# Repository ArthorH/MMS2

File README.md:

# modular_system_mini
mini verison of modular system connectable as bus 

# if you want to add new board
1. create new folder with name of the board
2. create new project in kicad in this folder

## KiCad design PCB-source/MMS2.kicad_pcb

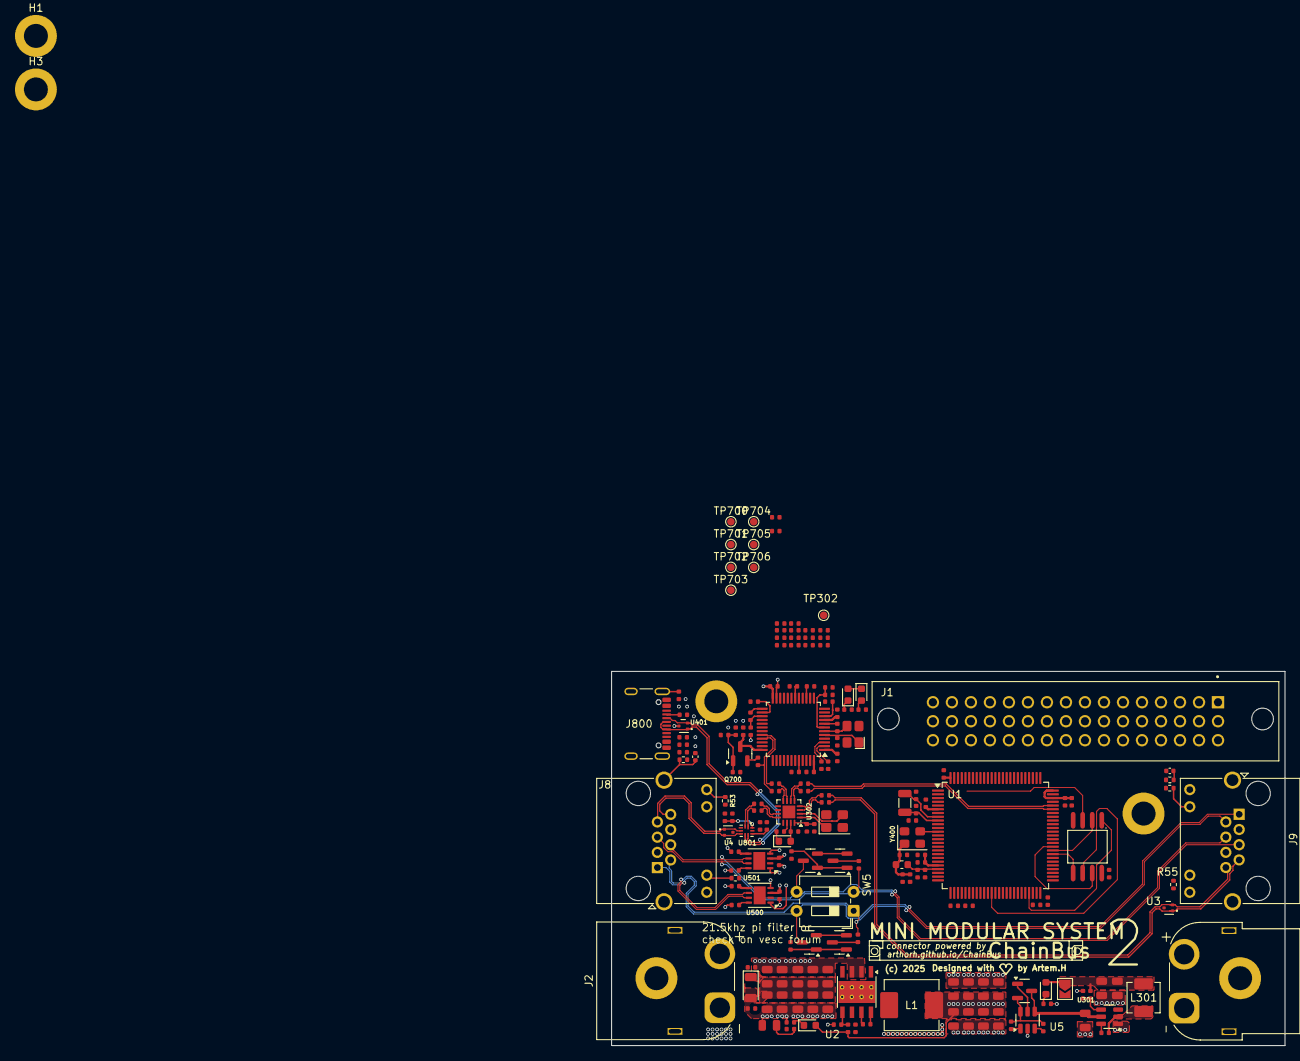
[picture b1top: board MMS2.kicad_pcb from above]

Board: 2 copper layers, 90.0 x 50.0 mm, 188 parts (0 on the bottom side), 120 nets.

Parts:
C1, C2, C4, C5, C6, C7, C14, C15, C16: 10uF; C_0805
C3, C10, C17, C100, C312, C401, C402, C404, C405, C406, C415, C416, C420, C421, C422, C424, C426, C432, C500, C501, C502, C503, C701, C702, C703, C704, C705, C706, C800, C801, C900: 100nF; C_0402
C8, C9: 220nF; C_0805
C11, C12, C13, C18, C19, C20, C22, C23, C24, C25, C28: 22uF; C_0805
C27, C700, C904: 1uF; C_0402
C45, C46: 10n; C_0402_1005Metric
C313, C314: 18pF; C_0402
C400, C403, C423, C425, C902: 10uF; C_0402
C410: 4.7uF; C_0402
C427, C434: 2.2uF; C_0402
C707, C708: 33pF; C_0402
D1: SMF58CA; D_SOD-123FL
D2, D301, D402, D700, D701: Red; D_0603
FB401: FB_0603
H1, H2, H3, H4, H4#2, H4#3: M3 mount; MountingHole_3.2mm_M3_DIN965_Pad
J1: 86093488324755V1LF; AMPHENOL_86093488324755V1LF
J2: AMASS XT60; AMASS_XT60PW-M_1x02_P7.20mm_Horizontal
J7: AMASS XT60; AMASS_XT60PW-F_1x02_P7.20mm_Horizontal
J8, J9: RJ45_LED_Shielded; RJ45_Amphenol_RJHSE538X
J800: USB_C_Receptacle_USB2.0_16P; USB_C_Receptacle_GCT_USB4105-xx-A_16P_TopMnt_Horizontal
JP301: SolderJumper_2_Bridged; SolderJumper-2_P1.3mm_Open_TrianglePad1.0x1.5mm
L1: CMPI0630-100M 10uH 4A; L_TechFuse_SL0620
L301: 3.3uH; L_Changjiang_FXL0420
Q2, Q3, Q5, Q6, Q7: AO3400A; Q_SOT-23
Q700: MMST3904; SOT-23
R1, R2: 120Ω; R_0402
R3, R5, R7, R10, R307, R402, R403, R405, R500, R501, R701, R703, R705, R706, R707, R709, R713, R802, R804: 10kΩ; R_0402
R4, R8, R9: 24.9kΩ; R_0402
R6, R700, R702: 100kΩ; R_0402
R11: 33.2kΩ; R_0402
R12, R400, R712: 1.2kΩ; R_0402
R13: 680Ω; R_0402
R14, R15, R704, R708, R715, R716, R900, R901, R902, R903, R906, R907: 22Ω; R_0402
R51, R56: 33k; R_0402_1005Metric
R52, R53, R54, R55: 1k; R_0402_1005Metric
R308, R401: 1kΩ; R_0402
R404, R406, R409, R710, R714: 100Ω; R_0402
R407, R408: 220Ω; R_0402
R711: 39kΩ; R_0402
R800, R801: 5.1kΩ; R_0402
R803: 22kΩ; R_0402
R805: 330Ω; R_0402
SW5: SW_DIP_x02; SW_DIP_SPSTx02_Slide_6.7x6.64mm_W7.62mm_P2.54mm_LowProfile
TP302, TP700, TP701, TP702, TP703, TP704, TP705, TP706: TestPoint; TestPoint_Pad_D1.0mm
U1: STM32H563VGTx; LQFP-100_14x14mm_P0.5mm
U2: LMR36520ADDAR; Texas_HSOP-8-1EP_3.9x4.9mm_P1.27mm_ThermalVias
U3, U4, U401: TPD2EUSB30DRTR-TP; SOT-723
U5: LM74700; SOT-23-6
U100: W25Q128; SOIC-8_L5.3-W5.3-P1.27-LS8.0-BL
U301: TPS563200; SOT-23-6
U302: CH334P; QFN-16-1EP_3x3mm_P0.5mm_EP1.7x1.7mm
U500, U501: TJA1044GTK_3Z; HVSON-8-1EP_3x3mm_P0.65mm_EP1.6x2.4mm
U700: STM32F103CBTx; LQFP-48_7x7mm_P0.5mm
U801: FSUSB42UMX; UFQFN-10_1.4x1.8
X300: Q13FC1350000400; FC-135R_L3.2-W1.5
Y400: ASE-xxxMHz; Oscillator_SMD_Abracon_ASE-4Pin_3.2x2.5mm
Y700: Crystal_GND24; CRYSTAL-SMD_4P-L3.2-W2.5-BL
Y900: Crystal_GND24; Crystal_SMD_3225-4Pin_3.2x2.5mm

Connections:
+3V3: C100.1, C312.1, C400.1, C401.1, C402.1, C403.1, C404.1, C405.1, C406.1, C420.1, C421.1, C422.1, C425.1, C426.1, C432.1, C501.1, C503.1, C700.1, C701.1, C702.1, C703.1, C704.1, C705.1, FB401.2, Q700.3 (C), R403.1, R405.1, R409.1, R700.1, R701.1, R707.1, TP702.1, U1.6 (VBAT), U1.11 (VDD), U1.21 (VREF+), U1.28 (VDD), U1.50 (VDD), U1.73 (VDDUSB), U1.75 (VDD), U1.100 (VDD), U100.8 (VCC), U500.5 (VIO), U501.5 (VIO), U700.1 (VBAT), U700.9 (VDDA), U700.24 (VDD), U700.36 (VDD), U700.48 (VDD), U801.9 (VCC), Y400.1 (EN), Y400.4 (Vdd)
+5V: C500.2, C502.2, C904.1, D301.2, R709.1, U302.15 (5V), U500.3 (VCC), U501.3 (VCC)
+12V: J8.6, J9.6
/CAN auto terminator/CAN1.+: J8.5, J9.5, R2.1, SW5.2, U501.7 (CANH)
/CAN auto terminator/CAN1.-: J8.4, J9.4, Q6.3 (D), SW5.3, U501.6 (CANL)
/CAN auto terminator/CAN2.+: J8.2, J9.2, R1.1, SW5.1, U500.7 (CANH)
/CAN auto terminator/CAN2.-: J8.1, J9.1, Q3.3 (D), SW5.4, U500.6 (CANL)
/CAN auto terminator/CAN_AUTOTERM.1: Q5.1 (G), Q6.1 (G), R3.1
/CAN auto terminator/CAN_AUTOTERM.2: Q2.1 (G), Q3.1 (G), R5.1
/CAN_TR1/CAN.RX: U1.81 (PD0), U500.4 (RXD)
/CAN_TR1/CAN.TX: U1.82 (PD1), U500.1 (TXD)
/CAN_TR2/CAN.RX: U1.51 (PB12), U501.4 (RXD)
/CAN_TR2/CAN.TX: U1.52 (PB13), U501.1 (TXD)
/MCU/BOOT0: C410.1, R401.2, R402.1, U1.94 (BOOT0)
/MCU/BOOT_EN: R401.1, U1.93 (PB7)
/MCU/NRST: C415.1, R403.2, R404.1
/MCU/OSC32_IN: C314.1, U1.8 (PC14), X300.2
/MCU/OSC32_OUT: C313.1, U1.9 (PC15), X300.1
/MCU/OSC_IN: U1.12 (PH0), Y400.3 (OUT)
/MCU/QSPI1.CS: U1.47 (PB10), U100.1 (CS#)
/MCU/QSPI1.IO0: U1.58 (PD11), U100.5 (DI)
/MCU/QSPI1.IO1: U1.59 (PD12), U100.2 (DO)
/MCU/QSPI1.IO2: U1.1 (PE2), U100.3 (IO2)
/MCU/QSPI1.IO3: U1.60 (PD13), U100.7 (IO3)
/MCU/QSPI1.SCLK: U1.37 (PB2), U100.6 (CLK)
/MCU/STATUS_LED: R408.1, U1.4 (PE5)
/MCU/SWD.SWCLK: R704.2, R715.1, U1.76 (PA14(JTCK)
/MCU/SWD.SWDIO: R716.1, U1.72 (PA13(JTMS)
/MCU/SWD.~RST: R404.2, R708.1, U1.14 (NRST)
/MCU/USB_MCU.D+: R901.1, U1.71 (PA12)
/MCU/USB_MCU.D-: R900.1, U1.70 (PA11)
/MCU/USER_LED_1: R400.1, U1.2 (PE3)
/MCU/USER_LED_2: R407.1, U1.3 (PE4)
/MCU/USR_BTN: C416.1, R405.2, R406.1
/MCU/USR_BUTTON: R406.2, U1.5 (PE6)
/MCU/VCAP_1: C427.1, U1.48 (VCAP)
/MCU/VCAP_2: C434.1, U1.98 (VCAP)
/MCU/VDDA: C423.1, C424.1, FB401.1, U1.22 (VDDA)
/MMS_CONNECTOR_DOWNSTREAM/USB_MMS_CONN.D+: J9.8, R903.1, U3.2
/MMS_CONNECTOR_DOWNSTREAM/USB_MMS_CONN.D-: J9.7, R902.1, U3.1
/MMS_CONNECTOR_UPSTREAM/USB_MMS_CONN.D+: J8.8, U4.2, U801.5 (HSD1+)
/MMS_CONNECTOR_UPSTREAM/USB_MMS_CONN.D-: J8.7, U4.1, U801.4 (HSD1-)
/STlink-BMprobe/CLK: TP705.1, U700.37 (PA14)
/STlink-BMprobe/DIO: TP704.1, U700.34 (PA13)
/STlink-BMprobe/LED: D700.1, D701.2, U700.30 (PA9)
/STlink-BMprobe/ST-LINK.D+: R712.2, R907.1, U700.33 (PA12)
/STlink-BMprobe/ST-LINK.D-: R906.1, U700.32 (PA11)
/STlink-BMprobe/STLINK-BOOT0: R702.2, TP703.1, U700.44 (BOOT0)
/STlink-BMprobe/STLINK-OSC_IN: C707.1, U700.5 (PD0), Y700.1
/STlink-BMprobe/STLINK-OSC_OUT: C708.1, U700.6 (PD1), Y700.3
/STlink-BMprobe/STLINK-RST: C706.1, R700.2, U700.7 (NRST)
/STlink-BMprobe/STLINK_RX: TP701.1, U700.13 (PA3)
/STlink-BMprobe/STLINK_TX: TP700.1, U700.12 (PA2)
/STlink-BMprobe/USB_RENUM: R710.2, U700.38 (PA15)
/USB HUB/USBIN1.D+: R14.2, U801.1 (D+)
/USB HUB/USBIN1.D-: R15.2, U801.2 (D-)
/USB HUB/USBIN1_R.D+: R14.1, U302.12 (DPU)
/USB HUB/USBIN1_R.D-: R15.1, U302.11 (DMU)
/USB HUB/USBOUT1_R.D+: R903.2, U302.4 (DP4)
/USB HUB/USBOUT1_R.D-: R902.2, U302.3 (DM4)
/USB HUB/USBOUT2_R.D+: R907.2, U302.8 (DP2)
/USB HUB/USBOUT2_R.D-: R906.2, U302.7 (DM2)
/USB HUB/USB_MCU_R.D+: R901.2, U302.6 (DP3)
/USB HUB/USB_MCU_R.D-: R900.2, U302.5 (DM3)
/USB switch/USBC_CONN.D+: J800.A6 (D+), J800.B6 (D+), U401.1, U801.7 (HSD2+)
/USB switch/USBC_CONN.D-: J800.A7 (D-), J800.B7 (D-), U401.2, U801.6 (HSD2-)
/USBC_CONN/CC1: J800.A5 (CC1), R801.1
/USBC_CONN/CC2: J800.B5 (CC2), R800.1
/VRM/LMR36520ADDAR/BOOT: C10.1, U2.7 (BOOT)
/VRM/LMR36520ADDAR/Cap_protec: C1.2, C2.1, C4.2, C5.1, C6.2, C7.1, C8.2, C9.1, C14.2, C15.1, D1.1, R8.2, R9.1
/VRM/LMR36520ADDAR/FB: R4.1, R6.2, U2.5 (FB)
/VRM/LMR36520ADDAR/LMR36520ADDAR_VOUT: C3.2, C11.1, C12.1, C13.1, C22.1, C23.1, C24.1, C25.1, C27.1, C28.1, D402.2, L1.2, Q7.2 (S), R6.1, R7.1, U5.6 (ANODE)
/VRM/LMR36520ADDAR/PG: R10.1, U2.4 (PG)
/VRM/LMR36520ADDAR/SW: C10.2, L1.1, U2.8 (SW)
/VRM/LMR36520ADDAR/VCC: C16.1, R10.2, U2.6 (VCC)
/VRM/TPS563201/+3V3_UNPROTEC: C18.1, C20.1, D2.2, JP301.1 (A), L301.2, R11.1
/VRM/TPS563201/FB_3V3: R11.2, R307.1, TP302.1, U301.4 (VFB)
/VRM/TPS563201/SW_3V3: C17.1, L301.1, U301.2 (SW)
/VRM/TPS563201/VBST_3V3: C17.2, U301.6 (VBST)
BRD_VIN: C1.1, C4.1, C6.1, C8.1, C14.1, J2.2, J7.2, R8.1, U2.2 (VIN), U2.3 (EN)
GND: C2.2, C5.2, C7.2, C9.2, C11.2, C12.2, C13.2, C15.2, C16.2, C18.2, C19.2, C20.2, C22.2, C23.2, C24.2, C25.2, C27.2, C28.2, C45.2, C46.2, C100.2, C312.2, C313.2, C314.2, C400.2, C401.2, C402.2, C403.2, C404.2, C405.2, C406.2, C410.2, C415.2, C416.2, C420.2, C421.2, C422.2, C423.2, C424.2, C425.2, C426.2, C427.2, C432.2, C434.2, C500.1, C501.2, C502.1, C503.2, C700.2, C701.2, C702.2, C703.2, C704.2, C705.2, C706.2, C707.2, C708.2, C800.2, C801.2, C900.2, C902.2, C904.2, D1.2, H1.1, J8.3, J8.9, J8.11, J9.3, J9.9, J9.11, J800.A1 (GND), J800.A12 (GND), J800.B1 (GND), J800.B12 (GND), R3.2, R4.2, R5.2, R9.2, R12.2, R13.2, R51.2, R56.2, R307.2, R402.2, R500.2, R501.2, R702.1, R703.2, R705.1, R706.1, R711.2, R713.2, R800.2, R801.2, R803.2, R804.2, R805.2, TP706.1, U1.10 (VSS), U1.19 (VSSA), U1.20 (VREF-), U1.27 (VSS), U1.49 (VSS), U1.74 (VSS), U1.99 (VSS), U2.1 (GND), U2.9 (GND), U3.3, U4.3, U5.2 (GND), U100.4 (GND), U301.1 (GND), U302.17 (GND), U401.3, U500.2 (GND), U500.9 (EP), U501.2 (GND), U501.9 (EP), U700.8 (VSSA), U700.23 (VSS), U700.35 (VSS), U700.47 (VSS), U801.3 (GND), Y400.2 (GND), Y700.2, Y700.4, Y900.2, Y900.4
GNDPWR: J2.1, J7.1
unnamed: C45.1, J8.SH, R51.1
unnamed: C46.1, J9.SH, R56.1
unnamed: D2.1, R13.1
unnamed: D301.1, R308.2
unnamed: D402.1, R12.1
unnamed: D700.2, R707.2
unnamed: D701.1, R713.1
unnamed: J8.10, R52.2
unnamed: J8.12, R53.2
unnamed: J9.10, R54.2
unnamed: J9.12, R55.2
unnamed: C801.1, J800.S1 (SHIELD), R805.1
unnamed: Q2.3 (D), R1.2
unnamed: Q2.2 (S), Q3.2 (S)
unnamed: Q5.3 (D), R2.2
unnamed: Q5.2 (S), Q6.2 (S)
unnamed: Q7.1 (G), U5.5 (GATE)
unnamed: Q700.1 (B), R709.2, R710.1, R711.1
unnamed: Q700.2 (E), R712.1
unnamed: R7.2, U5.3 (EN)
unnamed: C3.1, U5.1 (VCAP)
unnamed: C900.1, C902.1, U302.16 (3V3)
unnamed: R308.1, U302.14 (PGANG)
unnamed: U302.2 (XI), Y900.3
unnamed: U302.1 (XO), Y900.1
unnamed: R500.1, U500.8 (STB)
unnamed: R501.1, U501.8 (STB)
unnamed: R701.2, R703.1, U700.10 (PA0)
unnamed: R704.1, U700.15 (PA5)
unnamed: R708.2, U700.18 (PB0)
unnamed: R714.2, U700.25 (PB12)
unnamed: R715.2, U700.26 (PB13)
unnamed: R714.1, R716.2, U700.27 (PB14)
unnamed: R705.2, U700.2 (PC13)
unnamed: R706.2, U700.3 (PC14)
unnamed: R802.2, R803.1, U801.10 (SEL)
unnamed: R804.1, U801.8 (~OE)
VBUS: C19.1, C800.1, J800.A4 (VBUS), J800.A9 (VBUS), J800.B4 (VBUS), J800.B9 (VBUS), Q7.3 (D), R802.1, U5.4 (CATHODE), U301.3 (VIN), U301.5 (EN)

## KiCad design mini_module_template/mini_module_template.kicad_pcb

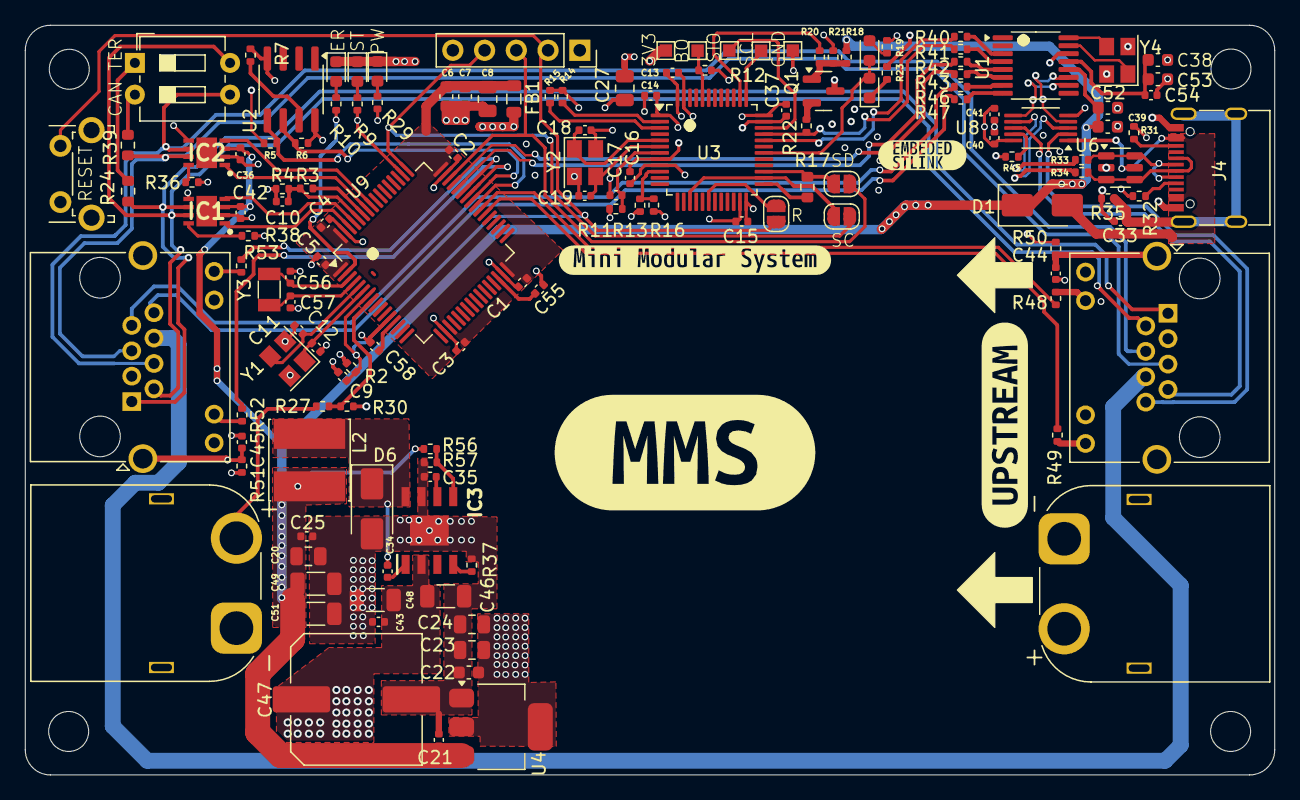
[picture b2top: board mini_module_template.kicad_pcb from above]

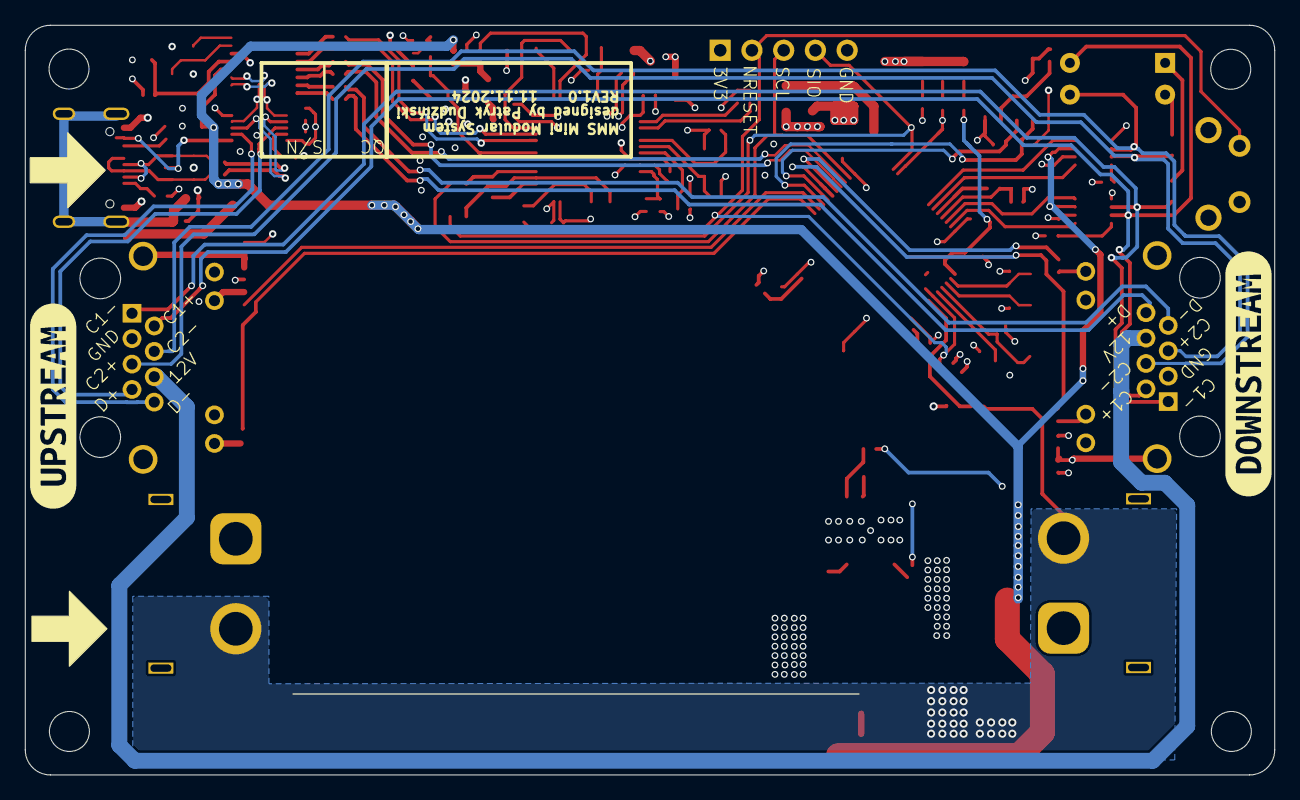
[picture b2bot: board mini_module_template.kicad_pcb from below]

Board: 4 copper layers, 100.0 x 60.0 mm, 150 parts (2 on the bottom side), 99 nets.

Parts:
C1, C2, C3, C4, C5, C9, C21, C25, C34, C35, C36, C40, C42, C43, C54, C58: 100n; C_0402_1005Metric
C6, C53: 1u; C_0603_1608Metric
C7: 4.7u; C_0603_1608Metric
C8, C20, C23, C24, C27: 10u; C_0805_2012Metric
C10: 4.7u; C_0402_1005Metric
C11, C12: 17p; C_0402_1005Metric
C13, C14, C15, C16, C17, C37: 100nF; C_0402_1005Metric
C18, C19: 20pF; C_0402_1005Metric
C22, C52: 100n; C_0603_1608Metric
C33, C44, C45: 10n; C_0402_1005Metric
C38, C39: 10u; C_0603_1608Metric
C41: 1n; C_0402_1005Metric
C46, C48: 2.2u; C_1206_3216Metric
C47: 47u; C_Elec_10x10.2
C49, C51: 47u; C_1206_3216Metric
C55: 2.2u; C_0402_1005Metric
C56, C57: 6P; C_0402_1005Metric
D1: ss34; D_SMA
D2: USR_LED1; D_0603_1608Metric
D3: USR_LED2; D_0603_1608Metric
D4: BLUE; LED_0603_1608Metric
D5: RED; LED_0603_1608Metric
D6: SS34; D_SMA
D7: LV_PWR; D_0603_1608Metric
FB1: FerriteBead; L_0805_2012Metric
H1, H2, H3, H4: MountingHole_3.2mm_M3
IC1, IC2: TJA1044GTK_3Z; SON65P300X300X100-9N-D
IC3: LMR16030SDDAR; SOIC127P600X170-9N
J1: SWD; PinSocket_1x05_P2.54mm_Vertical
J2, J6: Conn_01x02; AMASS_XT60PW-M_1x02_P7.20mm_Horizontal
J4: USB_C_Receptacle_USB2.0; USB_C_Receptacle_G-Switch_GT-USB-7010ASV
J7, J8: RJ45_LED_Shielded; RJ45_Amphenol_RJHSE538X
JP1, JP2, JP3: SolderJumper_2_Bridged; SolderJumper-2_P1.3mm_Open_RoundedPad1.0x1.5mm
L2: 8.2u; L_Cenker_CKCS6045
Q1: S9013; SOT-23
R2, R4, R7, R14, R18, R36, R38, R45: 10k; R_0402_1005Metric
R3, R9, R10, R30, R48, R49, R52, R53: 1k; R_0402_1005Metric
R5, R6, R13, R16, R31, R32: 4k7; R_0402_1005Metric
R11, R12, R56: 100k; R_0402_1005Metric
R15: DNP; R_0402_1005Metric
R17: 100R; R_0603_1608Metric
R19, R23: 220R; R_0402_1005Metric
R20: 100R; R_0402_1005Metric
R21: 39k; R_0402_1005Metric
R22: 1K5; R_0402_1005Metric
R24, R39: 120R; R_0603_1608Metric
R27: 43k; R_0402_1005Metric
R29: 220; R_0402_1005Metric
R33, R34, R40, R41, R42, R43, R46, R47: 22R; R_0402_1005Metric
R35, R50, R51: 33k; R_0402_1005Metric
R37: 49,9k; R_0402_1005Metric
R57: 17,8k; R_0402_1005Metric
SW2: NRST; SW_Tactile_SPST_Angled_PTS645Vx58-2LFS
SW5: SW_DIP_x02; SW_DIP_SPSTx02_Slide_6.7x6.64mm_W7.62mm_P2.54mm_LowProfile
TP1, TP2, TP3, TP4, TP5: TestPoint_Pad_1.0x1.0mm
U1: CH334R; QSOP-16_3.9x4.9mm_P0.635mm
U2: FM24CL16B; SOIC-8_3.9x4.9mm_P1.27mm
U3: STM32F103CB; LQFP-48_7x7mm_P0.5mm
U4: AZ1117-3.3; SOT-223-3_TabPin2
U6: IP4220CZ6; SOT-23-6
U8: TS3USB30EDGSR; VSSOP-10_3x3mm_P0.5mm
U9: STM32F446RETx; LQFP-64_10x10mm_P0.5mm
Y1, Y2: 8MHz; Crystal_SMD_3225-4Pin_3.2x2.5mm
Y3: 32.768kHz; Crystal_SMD_3215-2Pin_3.2x1.5mm
Y4: 12Mhz; Crystal_SMD_3225-4Pin_3.2x2.5mm
kibuzzard-674CE2D2: G***; kibuzzard-674CE2D2
kibuzzard-67314D46: G***; kibuzzard-67314D46
kibuzzard-673147F0, kibuzzard-673147F0#2: G***; kibuzzard-673147F0
kibuzzard-673151BF: G***; kibuzzard-673151BF
kibuzzard-67314807: G***; kibuzzard-67314807

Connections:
+3V3: C13.1, C14.1, C15.1, C16.1, C22.1, C23.1, C24.1, C27.1, C37.1, C40.1, C41.1, FB1.2, IC1.5 (VIO), IC2.5 (VIO), J1.1, Q1.3 (C), R2.1, R5.1, R6.1, R11.2, R13.2, R19.2, R29.1, TP1.1, U2.8 (VDD), U3.1 (VBAT), U3.9 (VDDA), U3.24 (VDD), U3.36 (VDD), U3.48 (VDD), U4.2 (VO), U8.10 (VCC)
+5V: C20.1, C21.1, C25.1, C36.1, C39.2, C42.1, C49.1, C51.1, C52.2, D1.1 (K), IC1.3 (VCC), IC2.3 (VCC), L2.2, R18.2, R56.1, U1.12 (V5), U4.3 (VI)
+12V: J7.6, J8.6
/CAN/CAN1+: IC1.7 (CANH), J7.2, J8.2, SW5.4
/CAN/CAN1-: IC1.6 (CANL), J7.1, J8.1, R24.1
/CAN/CAN1_RXD: IC1.4 (RXD), U9.61 (PB8)
/CAN/CAN1_TXD: IC1.1 (TXD), U9.62 (PB9)
/CAN/CAN2+: IC2.7 (CANH), J7.5, J8.5, R39.1
/CAN/CAN2-: IC2.6 (CANL), J7.4, J8.4, SW5.3
/CAN/CAN2_RXD: IC2.4 (RXD), U9.57 (PB5)
/CAN/CAN2_TXD: IC2.1 (TXD), U9.58 (PB6)
/CAN/RXD1_LED: R48.1, U9.39 (PC8)
/CAN/RXD2_LED: R52.1, U9.42 (PA9)
/CAN/TXD1_LED: R49.1, U9.38 (PC7)
/CAN/TXD2_LED: R53.1, U9.43 (PA10)
/CAN/USB_DOWNSTREAM_D+: J8.8, R47.1
/CAN/USB_DOWNSTREAM_D-: J8.7, R46.2
/CAN/USB_UPSTREAM_D+: J7.8, U8.2 (D1+)
/CAN/USB_UPSTREAM_D-: J7.7, U8.8 (D1-)
/MCU/3V3_MCU: C1.1, C2.1, C3.1, C4.1, C5.1, C6.1, C7.1, C8.1, C58.1, FB1.1, U9.1 (VBAT), U9.13 (VDDA), U9.19 (VDD), U9.32 (VDD), U9.48 (VDD), U9.64 (VDD)
/MCU/BOOT0: C10.1, R3.2, R4.1, U9.60 (BOOT0)
/MCU/BOOT_EN: R3.1, U9.59 (PB7)
/MCU/I2C3_SCL: R6.2, U2.6 (SCL), U9.41 (PA8)
/MCU/I2C3_SDA: R5.2, U2.5 (SDA), U9.40 (PC9)
/MCU/NRST: C9.1, J1.2, JP3.1 (A), R2.2, SW2.2, U9.7 (NRST)
/MCU/SWCLK: J1.4, JP1.1 (A), U9.49 (PA14)
/MCU/SWDIO: J1.3, JP2.1 (A), U9.46 (PA13)
/MCU/USB_D+: R43.1, U9.45 (PA12)
/MCU/USB_D-: R42.1, U9.44 (PA11)
/MCU/USR_LED1: R9.1, U9.50 (PA15)
/MCU/USR_LED2: R10.1, U9.2 (PC13)
/MCU/V_SENSE: R27.2, R30.1, U9.8 (PC0)
/POWER/5V_COIL: C34.2, D6.1 (K), IC3.8 (SW), L2.1
/STLINK/BOOT: R12.2, TP2.1, U3.44 (BOOT0)
/STLINK/CLK: TP4.1, U3.37 (PA14)
/STLINK/DIO: TP3.1, U3.34 (PA13)
/STLINK/LED: D4.1 (K), D5.2 (A), U3.30 (PA9)
/STLINK/NRST: JP3.2 (B), U3.18 (PB0)
/STLINK/SWCLK: JP1.2 (B), U3.15 (PA5), U3.26 (PB13)
/STLINK/SWDIO: JP2.2 (B), R17.2, U3.27 (PB14)
/STLINK/USB_D+: R22.1, R41.1, U3.33 (PA12)
/STLINK/USB_D-: R40.2, U3.32 (PA11)
/STLINK/USB_RENUM: R20.1, U3.38 (PA15)
/USB/USB_CONN_D+: J4.A6 (D+), J4.B6 (D+), R34.1, U6.3 (I/O2), U6.4 (I/O2)
/USB/USB_CONN_D-: J4.A7 (D-), J4.B7 (D-), R33.1, U6.1 (I/O1), U6.6 (I/O1)
/USB/USB_PROT_D+: R34.2, U8.3 (D2+)
/USB/USB_PROT_D-: R33.2, U8.7 (D2-)
/USB/USB_UPSTREAM_D+: U1.11 (DPU), U8.4 (D+)
/USB/USB_UPSTREAM_D-: U1.10 (DMU), U8.6 (D-)
/USB/VBUS: D1.2 (A), J4.A4 (VBUS), J4.A9 (VBUS), J4.B4 (VBUS), J4.B9 (VBUS), U6.5 (VBUS), U8.1 (S)
GND: C1.2, C2.2, C3.2, C4.2, C5.2, C6.2, C7.2, C8.2, C9.2, C10.2, C11.1, C12.1, C13.2, C14.2, C15.2, C16.2, C17.2, C18.2, C19.2, C20.2, C21.2, C22.2, C23.2, C24.2, C25.2, C27.2, C33.2, C35.1, C36.2, C37.2, C38.1, C39.1, C40.2, C41.2, C42.2, C43.2, C44.2, C45.2, C46.2, C47.2, C48.2, C49.2, C51.2, C52.1, C53.1, C54.1, C55.1, C56.1, C57.1, C58.2, D2.1 (K), D3.1 (K), D6.2 (A), D7.1 (K), IC1.2 (GND), IC2.2 (GND), IC3.7 (GND), IC3.9 (EP), J1.5, J2.1, J4.A1 (GND), J4.A12 (GND), J4.B1 (GND), J4.B12 (GND), J6.1, J7.3, J7.9, J7.11, J8.3, J8.9, J8.11, R4.2, R7.1, R12.1, R14.1, R15.1, R16.1, R21.1, R23.1, R30.2, R31.1, R32.1, R35.2, R36.1, R37.2, R38.1, R45.1, R50.2, R51.2, R57.2, SW2.1, TP5.1, U1.14 (GND), U2.4 (VSS), U3.8 (VSSA), U3.23 (VSS), U3.35 (VSS), U3.47 (VSS), U4.1 (GND), U6.2 (GND), U8.5 (GND), U9.12 (VSSA), U9.18 (VSS), U9.31 (VSS), U9.47 (VSS), U9.63 (VSS), Y1.2, Y1.4, Y2.2, Y2.4, Y4.2, Y4.4
unnamed: C44.1, J7.SH, R50.1
unnamed: C45.1, J8.SH, R51.1
unnamed: D2.2 (A), R9.2
unnamed: D3.2 (A), R10.2
unnamed: D4.2 (A), R19.1
unnamed: D5.1 (K), R23.2
unnamed: D7.2 (A), R29.2
unnamed: IC1.8 (STB), R38.2
unnamed: IC2.8 (STB), R36.2
unnamed: C34.1, IC3.1 (BOOT)
unnamed: IC3.5 (FB), R56.2, R57.1
unnamed: IC3.4 (RT/SYNC), R37.1
unnamed: C35.2, IC3.6 (SS)
unnamed: J4.A5 (CC1), R32.2
unnamed: J4.B5 (CC2), R31.2
unnamed: C33.1, J4.S1 (SHIELD), R35.1
unnamed: J7.10, R48.2
unnamed: J7.12, R49.2
unnamed: J8.10, R52.2
unnamed: J8.12, R53.2
unnamed: Q1.1 (B), R18.1, R20.2, R21.2
unnamed: Q1.2 (E), R22.2
unnamed: R24.2, SW5.1
unnamed: R39.2, SW5.2
unnamed: R46.1, U1.7 (DM1)
unnamed: R42.2, U1.5 (DM2)
unnamed: R40.1, U1.3 (DM3)
unnamed: R47.2, U1.8 (DP1)
unnamed: R43.2, U1.6 (DP2)
unnamed: R41.2, U1.4 (DP3)
unnamed: C38.2, C53.2, C54.2, U1.13 (VDD33)
unnamed: U1.16 (XI), Y4.3
unnamed: U1.15 (XO), Y4.1
unnamed: R7.2, U2.7 (WP)
unnamed: C17.1, R11.1, U3.7 (NRST)
unnamed: R13.1, R16.2, U3.10 (PA0)
unnamed: R17.1, U3.25 (PB12)
unnamed: R14.2, U3.2 (PC13)
unnamed: R15.2, U3.3 (PC14)
unnamed: C18.1, U3.5 (PD0), Y2.1
unnamed: C19.1, U3.6 (PD1), Y2.3
unnamed: R45.2, U8.9 (~OE)
unnamed: C56.2, U9.3 (PC14), Y3.1
unnamed: C57.2, U9.4 (PC15), Y3.2
unnamed: C11.2, U9.5 (PH0), Y1.3
unnamed: C12.2, U9.6 (PH1), Y1.1
unnamed: C55.2, U9.30 (VCAP_1)
VCC: C43.1, C46.1, C47.1, C48.1, IC3.2 (VIN), J2.2, J6.2, R27.1

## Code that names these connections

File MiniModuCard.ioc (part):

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Mcu.Name=STM32F446R(C-E)Tx
Mcu.Package=LQFP64
Mcu.UserName=STM32F446RETx
PA10.Signal=GPIO_Output
PA11.Mode=Device_Only
PA11.Signal=USB_OTG_FS_DM
PA12.Mode=Device_Only
PA12.Signal=USB_OTG_FS_DP
PA13.Mode=Serial_Wire
PA13.Signal=SYS_JTMS-SWDIO
PA14.Mode=Serial_Wire
PA14.Signal=SYS_JTCK-SWCLK
PA15.Signal=GPIO_Output
PA8.Mode=I2C
PA8.Signal=I2C3_SCL
PA9.Signal=GPIO_Output
PB5.Mode=CAN_Activate
PB5.Signal=CAN2_RX
PB6.Mode=CAN_Activate
PB6.Signal=CAN2_TX
PB7.Signal=GPIO_Output
PB8.Mode=CAN_Activate
PB8.Signal=CAN1_RX
PB9.Mode=CAN_Activate
PB9.Signal=CAN1_TX
PC0.Signal=ADCx_IN10
PC13.Signal=GPIO_Output
PC14-OSC32_IN.Mode=LSE-External-Oscillator
PC14-OSC32_IN.Signal=RCC_OSC32_IN
PC15-OSC32_OUT.Mode=LSE-External-Oscillator
PC15-OSC32_OUT.Signal=RCC_OSC32_OUT
PC7.Signal=GPIO_Output
PC8.Signal=GPIO_Output
PC9.Mode=I2C
PC9.Signal=I2C3_SDA
PH0-OSC_IN.Mode=HSE-External-Oscillator
PH0-OSC_IN.Signal=RCC_OSC_IN
PH1-OSC_OUT.Mode=HSE-External-Oscillator
PH1-OSC_OUT.Signal=RCC_OSC_OUT
board=custom

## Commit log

2024-10-27 init commit
2024-10-28 initial design
2024-10-28 update MScube config file
2024-11-01 Leyout rev 1
2024-11-02 addded crystal to usb hub. added connection tabs to stm+stlink
2024-11-03 added jcl gerebr for thearotical quote about 50$ with assemply for 5
2024-11-10 fixed can and usb traces
2024-11-11 rev 1.0 finished
2024-12-01 revison C, aded 2 can support and gight voltage input stepdown
2024-12-01 fix silkscreen
2024-12-02 changed rj45 conenctor to use differnt pinout with can
2024-12-05 update diff-traces and internal layer
2024-12-08 final check rev A
2024-12-14 fixed issue woth oncvorrect usb pin
2024-12-16 final rev
2025-01-27 cmall change
2025-03-13 updaet schematic
2025-07-13 Add LMR516x5 sym and to schematic
2025-08-09 vrm VIP
2025-08-17 Finish component and diffpair placement
2025-08-19 pinout start
2025-09-11 in progress
